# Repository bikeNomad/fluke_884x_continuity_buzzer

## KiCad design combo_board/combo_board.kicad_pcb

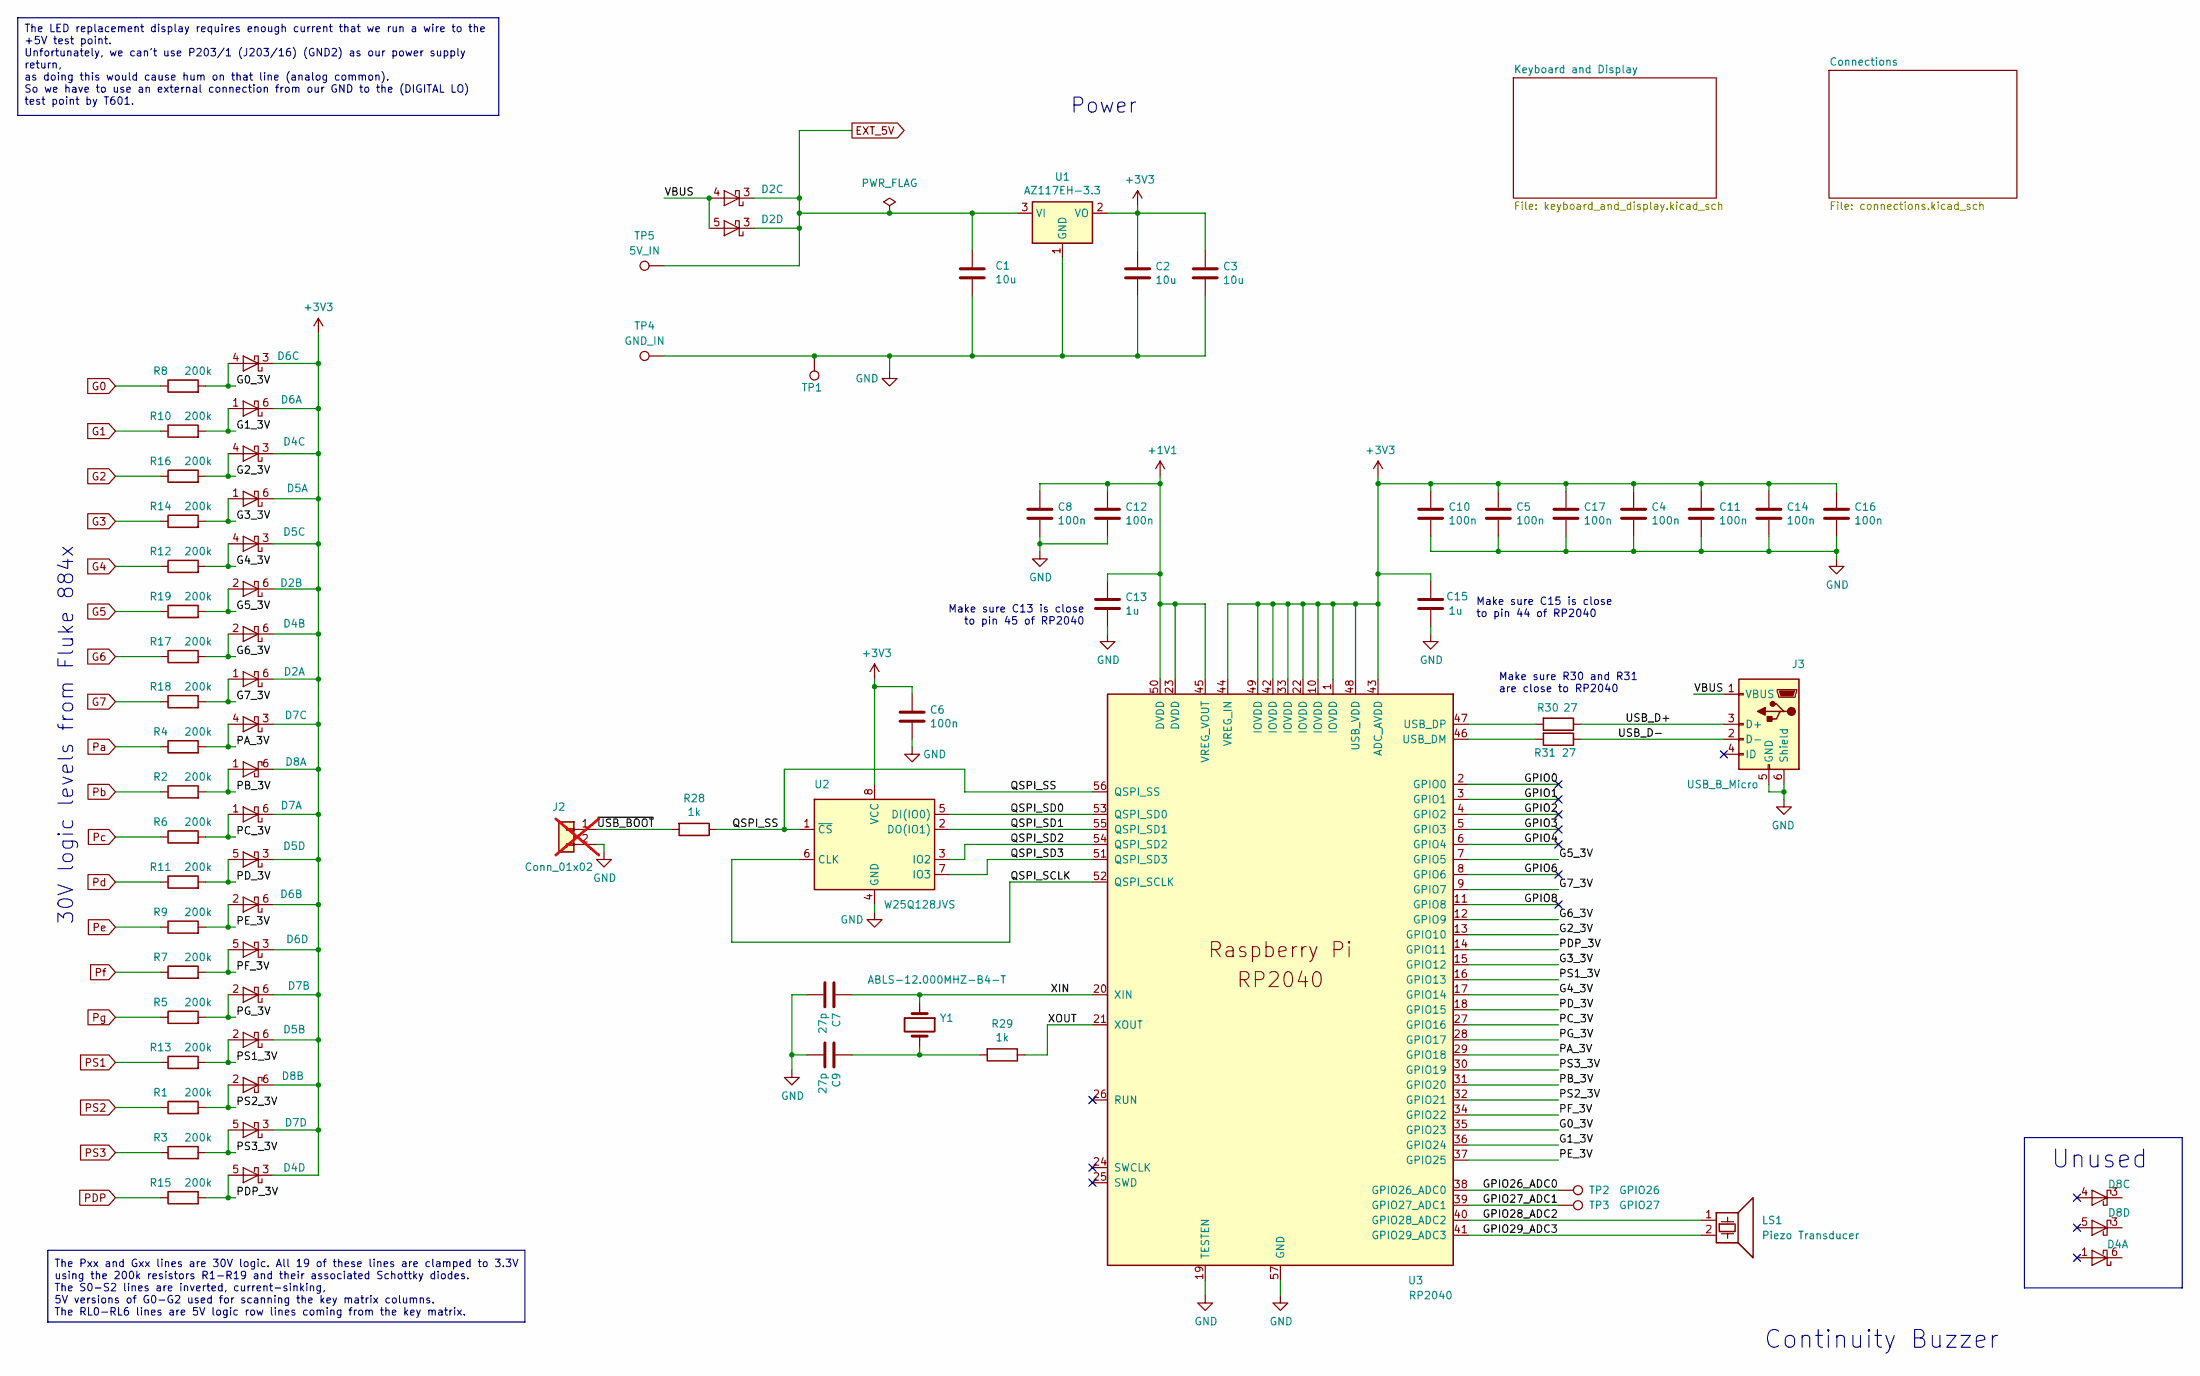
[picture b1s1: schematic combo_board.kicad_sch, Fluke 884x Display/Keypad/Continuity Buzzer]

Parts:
C1, C2, C3: 10u; C_0805_2012Metric; LCSC C15850
C4, C5, C6, C8, C10, C11, C12, C14, C16, C17: 100n; C_0402_1005Metric; LCSC C1525
C7, C9: 27p; C_0402_1005Metric; LCSC C1557
C13, C15: 1u; C_0402_1005Metric; LCSC C52923
D2, D4, D5, D6, D7, D8: BAT54CDW; SOT-363_SC-70-6; LCSC C5240639
J2: Conn_01x02; PinHeader_1x02_P2.54mm_Vertical; LCSC C2685154; not fitted
J3: USB_B_Micro; USB_Micro-B_Molex-105133-0001; LCSC C132563
LS1: Piezo Transducer; Buzzer_17x9RM10; LCSC C360609
R1, R2, R3, R4, R5, R6, R7, R8, R9, R10, R11, R12, R13, R14, R15, R16, R17, R18, R19: 200k; R_0402_1005Metric; LCSC C25764
R28, R29: 1k; R_0402_1005Metric; LCSC C11702
R30, R31: 27; R_0402_1005Metric; LCSC C25156
TP1: TestPoint; TestPoint_Keystone_5019_Minature; LCSC C238131
TP2: GPIO26; TestPoint_THTPad_1.0x1.0mm_Drill0.5mm
TP3: GPIO27; TestPoint_THTPad_1.0x1.0mm_Drill0.5mm
TP4: GND_IN; TestPoint_THTPad_D3.0mm_Drill1.5mm
TP5: 5V_IN; TestPoint_THTPad_D3.0mm_Drill1.5mm
U1: AZ117EH-3.3; SOT-223-3_TabPin2; LCSC C108494
U2: W25Q128JVS; SOIC-8_5.23x5.23mm_P1.27mm; LCSC C97521
U3: RP2040; RP2040-QFN-56; LCSC C2040
Y1: ABLS-12.000MHZ-B4-T; Crystal_SMD_HC49-US; LCSC C326543

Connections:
+1V1: C8.1, C12.1, C13.1, U3.23 (DVDD), U3.45 (VREG_VOUT), U3.50 (DVDD)
+3V3: C2.1, C3.1, C4.1, C5.1, C6.1, C10.1, C11.1, C14.1, C15.1, C16.1, C17.1, D2.6 (K), D4.3 (K), D4.6 (K), D5.3 (K), D5.6 (K), D6.3 (K), D6.6 (K), D7.3 (K), D7.6 (K), D8.6 (K), U1.2 (VO), U2.8 (VCC), U3.1 (IOVDD), U3.10 (IOVDD), U3.22 (IOVDD), U3.33 (IOVDD), U3.42 (IOVDD), U3.43 (ADC_AVDD), U3.44 (VREG_IN), U3.48 (USB_VDD), U3.49 (IOVDD)
/G0_3V: D6.4 (A), R8.2, U3.35 (GPIO23)
/G1_3V: D6.1 (A), R10.2, U3.36 (GPIO24)
/G2_3V: D4.4 (A), R16.2, U3.13 (GPIO10)
/G3_3V: D5.1 (A), R14.2, U3.15 (GPIO12)
/G4_3V: D5.4 (A), R12.2, U3.17 (GPIO14)
/G5_3V: D2.2 (A), R19.2, U3.7 (GPIO5)
/G6_3V: D4.2 (A), R17.2, U3.12 (GPIO9)
/G7_3V: D2.1 (A), R18.2, U3.9 (GPIO7)
/GPIO0: U3.2 (GPIO0)
/GPIO1: U3.3 (GPIO1)
/GPIO2: U3.4 (GPIO2)
/GPIO3: U3.5 (GPIO3)
/GPIO4: U3.6 (GPIO4)
/GPIO6: U3.8 (GPIO6)
/GPIO8: U3.11 (GPIO8)
/GPIO26_ADC0: TP2.1, U3.38 (GPIO26_ADC0)
/GPIO27_ADC1: TP3.1, U3.39 (GPIO27_ADC1)
/GPIO28_ADC2: LS1.1, U3.40 (GPIO28_ADC2)
/GPIO29_ADC3: LS1.2, U3.41 (GPIO29_ADC3)
/PA_3V: D7.4 (A), R4.2, U3.29 (GPIO18)
/PB_3V: D8.1 (A), R2.2, U3.31 (GPIO20)
/PC_3V: D7.1 (A), R6.2, U3.27 (GPIO16)
/PDP_3V: D4.5 (A), R15.2, U3.14 (GPIO11)
/PD_3V: D5.5 (A), R11.2, U3.18 (GPIO15)
/PE_3V: D6.2 (A), R9.2, U3.37 (GPIO25)
/PF_3V: D6.5 (A), R7.2, U3.34 (GPIO22)
/PG_3V: D7.2 (A), R5.2, U3.28 (GPIO17)
/PS1_3V: D5.2 (A), R13.2, U3.16 (GPIO13)
/PS2_3V: D8.2 (A), R1.2, U3.32 (GPIO21)
/PS3_3V: D7.5 (A), R3.2, U3.30 (GPIO19)
/QSPI_SCLK: U2.6 (CLK), U3.52 (QSPI_SCLK)
/QSPI_SD0: U2.5 (DI(IO0)), U3.53 (QSPI_SD0)
/QSPI_SD1: U2.2 (DO(IO1)), U3.55 (QSPI_SD1)
/QSPI_SD2: U2.3 (IO2), U3.54 (QSPI_SD2)
/QSPI_SD3: U2.7 (IO3), U3.51 (QSPI_SD3)
/QSPI_SS: R28.1, U2.1 (~CS), U3.56 (QSPI_SS)
/USB_D+: J3.3 (D+), R30.1
/USB_D-: J3.2 (D-), R31.1
/VBUS: D2.4 (A), D2.5 (A), J3.1 (VBUS)
/XIN: C7.1, U3.20 (XIN), Y1.1
/XOUT: R29.1, U3.21 (XOUT)
/~USB_BOOT: J2.1, R28.2
EXT_5V: C1.1, D2.3 (K), TP5.1, U1.3 (VI); also elsewhere on the board
G0: R8.1; also elsewhere on the board
G1: R10.1; also elsewhere on the board
G2: R16.1; also elsewhere on the board
G3: R14.1; also elsewhere on the board
G4: R12.1; also elsewhere on the board
G5: R19.1; also elsewhere on the board
G6: R17.1; also elsewhere on the board
G7: R18.1; also elsewhere on the board
GND: C1.2, C2.2, C3.2, C4.2, C5.2, C6.2, C7.2, C8.2, C9.2, C10.2, C11.2, C12.2, C13.2, C14.2, C15.2, C16.2, C17.2, J2.2, J3.5 (GND), J3.6 (Shield), TP1.1, TP4.1, U1.1 (GND), U2.4 (GND), U3.19 (TESTEN), U3.57 (GND); also elsewhere on the board
unnamed: C9.1, R29.2, Y1.2
unnamed: R31.2, U3.46 (USB_DM)
unnamed: R30.2, U3.47 (USB_DP)
PDP: R15.1; also elsewhere on the board
PS1: R13.1; also elsewhere on the board
PS2: R1.1; also elsewhere on the board
PS3: R3.1; also elsewhere on the board
Pa: R4.1; also elsewhere on the board
Pb: R2.1; also elsewhere on the board
Pc: R6.1; also elsewhere on the board
Pd: R11.1; also elsewhere on the board
Pe: R9.1; also elsewhere on the board
Pf: R7.1; also elsewhere on the board
Pg: R5.1; also elsewhere on the board

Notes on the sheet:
The LED replacement display requires enough current that we run a wire to the +5V test point. Unfortunately, we can't use P203/1 (J203/16) (GND2) as our power supply return, as doing this would cause hum on that line (analog common). So we have to use an external connection from our GND to the (DIG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
The Pxx and Gxx lines are 30V logic. All 19 of these lines are clamped to 3.3V using the 200k resistors R1-R19 and their associated Schottky diodes. The S0-S2 lines are inverted, current-sinking, 5V versions of G0-G2 used for scanning the key matrix columns. The RL0-RL6 lines are 5V logic row lines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
Unused
Power
30V logic levels from Fluke 884x
Make sure C15 is close to pin 44 of RP2040
Make sure R30 and R31 are close to RP2040
Make sure C13 is close to pin 45 of RP2040
Continuity Buzzer

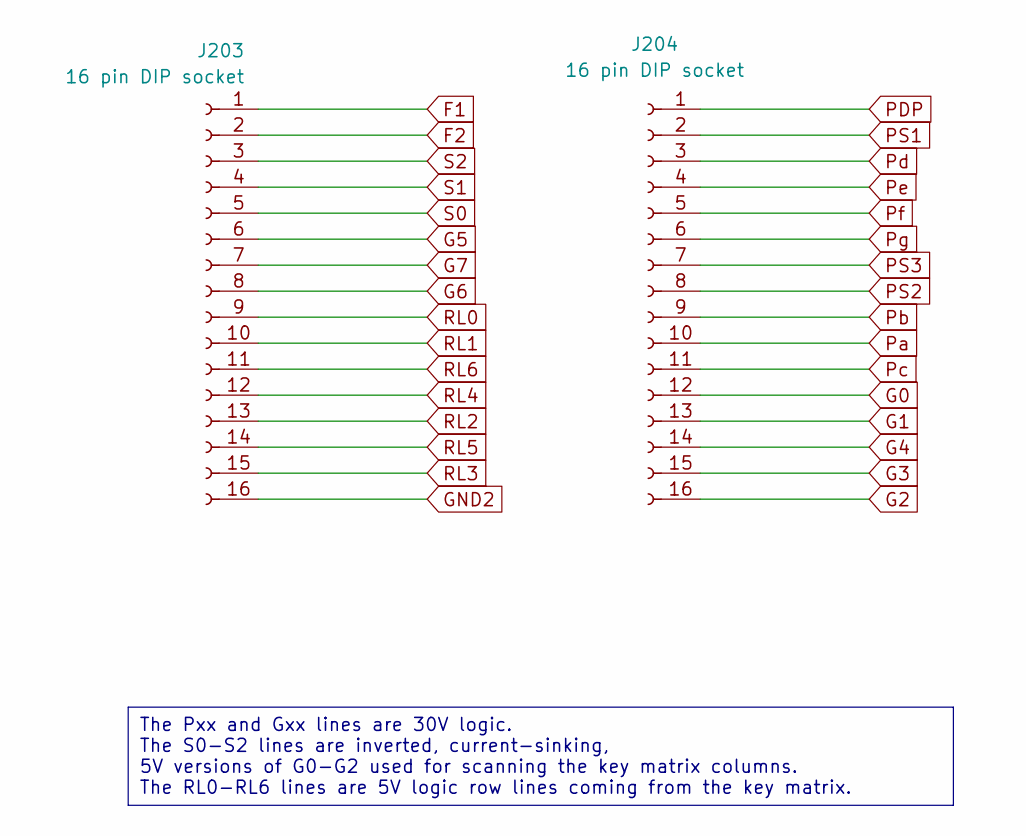
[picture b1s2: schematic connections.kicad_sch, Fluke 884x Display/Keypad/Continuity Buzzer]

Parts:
J203, J204: 16 pin DIP socket; DIP-16_W7.62mm_Socket; LCSC C157594

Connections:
F1: J203.1; also elsewhere on the board
F2: J203.2; also elsewhere on the board
G0: J204.12; also elsewhere on the board
G1: J204.13; also elsewhere on the board
G2: J204.16; also elsewhere on the board
G3: J204.15; also elsewhere on the board
G4: J204.14; also elsewhere on the board
G5: J203.6; also elsewhere on the board
G6: J203.8; also elsewhere on the board
G7: J203.7; also elsewhere on the board
GND2: J203.16
PDP: J204.1; also elsewhere on the board
PS1: J204.2; also elsewhere on the board
PS2: J204.8; also elsewhere on the board
PS3: J204.7; also elsewhere on the board
Pa: J204.10; also elsewhere on the board
Pb: J204.9; also elsewhere on the board
Pc: J204.11; also elsewhere on the board
Pd: J204.3; also elsewhere on the board
Pe: J204.4; also elsewhere on the board
Pf: J204.5; also elsewhere on the board
Pg: J204.6; also elsewhere on the board
RL0: J203.9; also elsewhere on the board
RL1: J203.10; also elsewhere on the board
RL2: J203.13; also elsewhere on the board
RL3: J203.15; also elsewhere on the board
RL4: J203.12; also elsewhere on the board
RL5: J203.14; also elsewhere on the board
RL6: J203.11; also elsewhere on the board
S0: J203.5; also elsewhere on the board
S1: J203.4; also elsewhere on the board
S2: J203.3; also elsewhere on the board

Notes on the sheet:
The Pxx and Gxx lines are 30V logic. The S0-S2 lines are inverted, current-sinking, 5V versions of G0-G2 used for scanning the key matrix columns. The RL0-RL6 lines are 5V logic row lines coming from the key matrix.

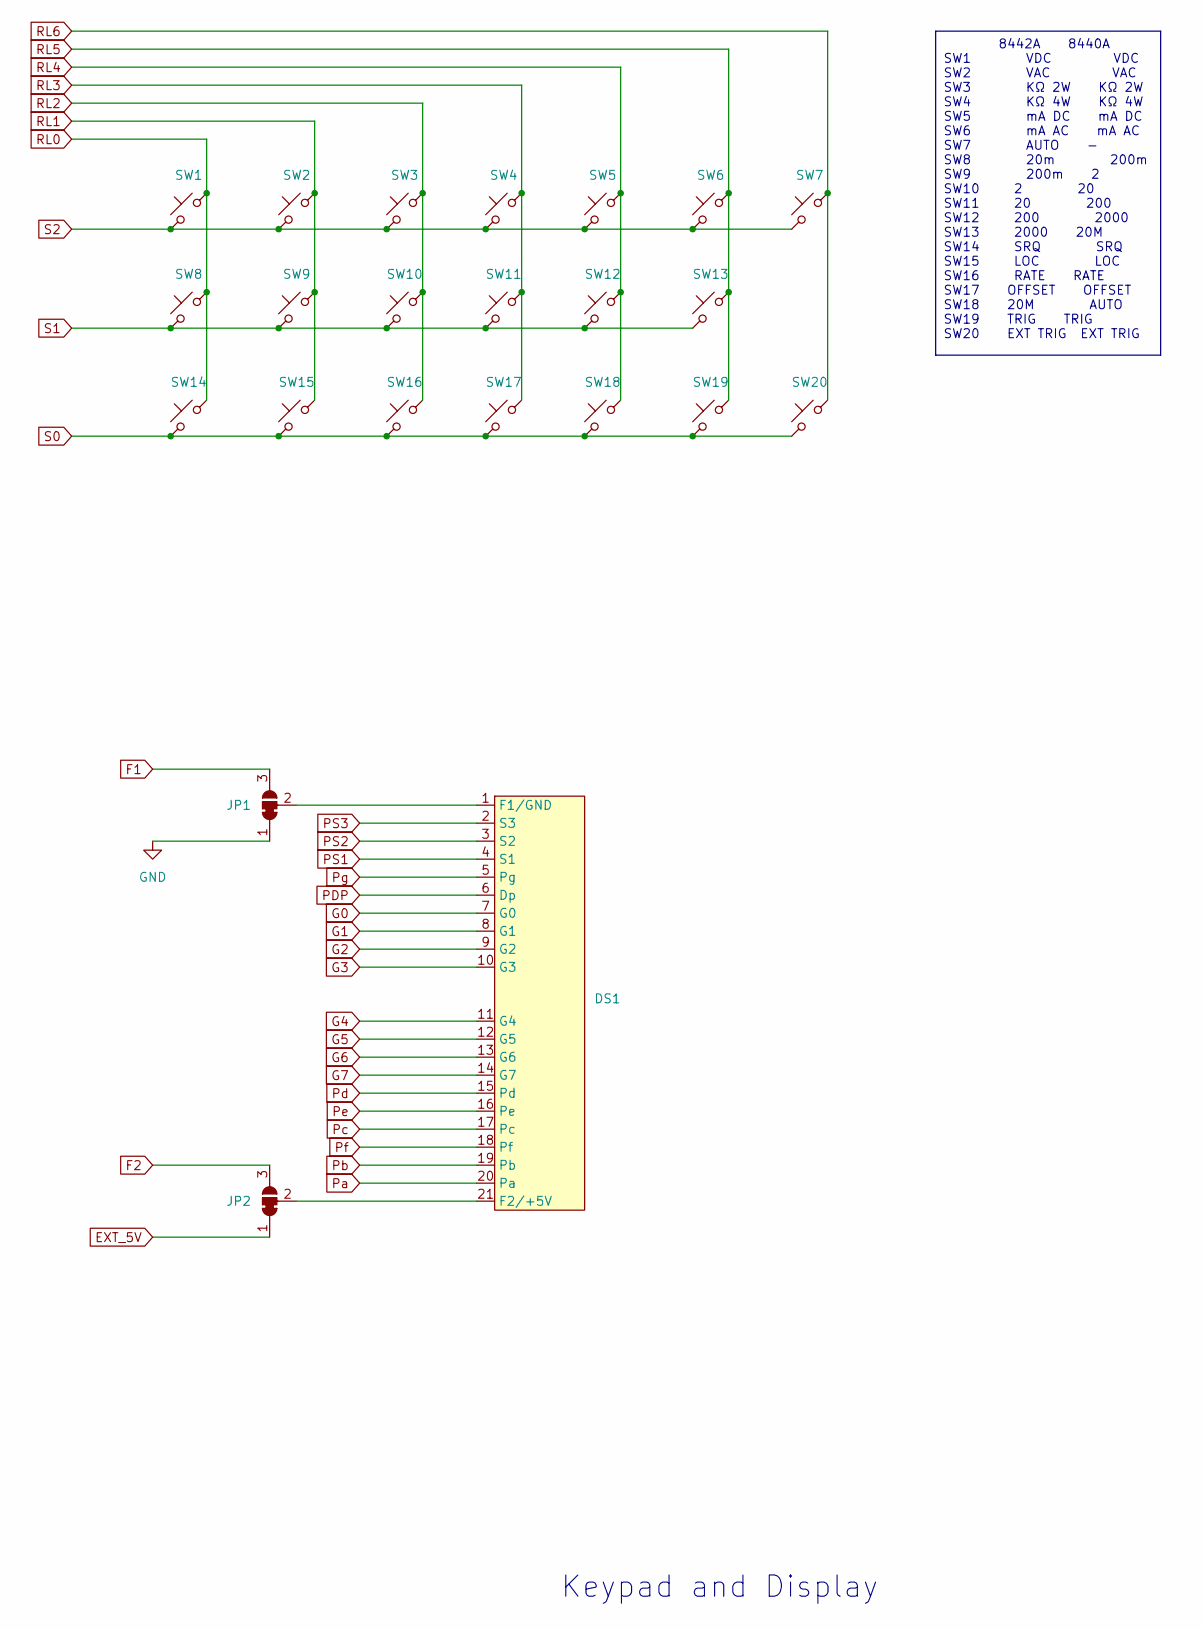
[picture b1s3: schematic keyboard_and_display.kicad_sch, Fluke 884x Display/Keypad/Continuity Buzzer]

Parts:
DS1: fluke_884x_display
JP1, JP2: SolderJumper_3_Bridged12; SolderJumper-3_P1.3mm_Bridged12_Pad1.0x1.5mm_NumberLabels
SW1, SW2, SW3, SW4, SW5, SW6, SW7, SW8, SW9, SW10, SW11, SW12, SW13, SW14, SW15, SW16, SW17, SW18, SW19, SW20: SW_Push_45deg; fluke_keypad_contact

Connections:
EXT_5V: JP2.1 (A); also elsewhere on the board
F1: JP1.3 (B); also elsewhere on the board
F2: JP2.3 (B); also elsewhere on the board
G0: DS1.7 (G0); also elsewhere on the board
G1: DS1.8 (G1); also elsewhere on the board
G2: DS1.9 (G2); also elsewhere on the board
G3: DS1.10 (G3); also elsewhere on the board
G4: DS1.11 (G4); also elsewhere on the board
G5: DS1.12 (G5); also elsewhere on the board
G6: DS1.13 (G6); also elsewhere on the board
G7: DS1.14 (G7); also elsewhere on the board
GND: JP1.1 (A); also elsewhere on the board
unnamed: DS1.1 (F1/GND), JP1.2 (C)
unnamed: DS1.21 (F2/+5V), JP2.2 (C)
PDP: DS1.6 (Dp); also elsewhere on the board
PS1: DS1.4 (S1); also elsewhere on the board
PS2: DS1.3 (S2); also elsewhere on the board
PS3: DS1.2 (S3); also elsewhere on the board
Pa: DS1.20 (Pa); also elsewhere on the board
Pb: DS1.19 (Pb); also elsewhere on the board
Pc: DS1.17 (Pc); also elsewhere on the board
Pd: DS1.15 (Pd); also elsewhere on the board
Pe: DS1.16 (Pe); also elsewhere on the board
Pf: DS1.18 (Pf); also elsewhere on the board
Pg: DS1.5 (Pg); also elsewhere on the board
RL0: SW1.1, SW8.1, SW14.1; also elsewhere on the board
RL1: SW2.1, SW9.1, SW15.1; also elsewhere on the board
RL2: SW3.1, SW10.1, SW16.1; also elsewhere on the board
RL3: SW4.1, SW11.1, SW17.1; also elsewhere on the board
RL4: SW5.1, SW12.1, SW18.1; also elsewhere on the board
RL5: SW6.1, SW13.1, SW19.1; also elsewhere on the board
RL6: SW7.1, SW20.1; also elsewhere on the board
S0: SW14.2, SW15.2, SW16.2, SW17.2, SW18.2, SW19.2, SW20.2; also elsewhere on the board
S1: SW8.2, SW9.2, SW10.2, SW11.2, SW12.2, SW13.2; also elsewhere on the board
S2: SW1.2, SW2.2, SW3.2, SW4.2, SW5.2, SW6.2, SW7.2; also elsewhere on the board

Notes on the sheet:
8442A 8440A SW1 VDC VDC SW2 VAC VAC SW3 KΩ 2W KΩ 2W SW4 KΩ 4W KΩ 4W SW5 mA DC mA DC SW6 mA AC mA AC SW7 AUTO - SW8 20m 200m SW9 200m 2 SW10 2 20 SW11 20 200 SW12 200 2000 SW13 2000 20M SW14 SRQ SRQ SW15 LOC LOC SW16 RATE RATE SW17 OFFSET OFFSET SW18 20M AUTO SW19 TRIG TRIG SW20 EXT TRIG EXT TRIG
Keypad and Display

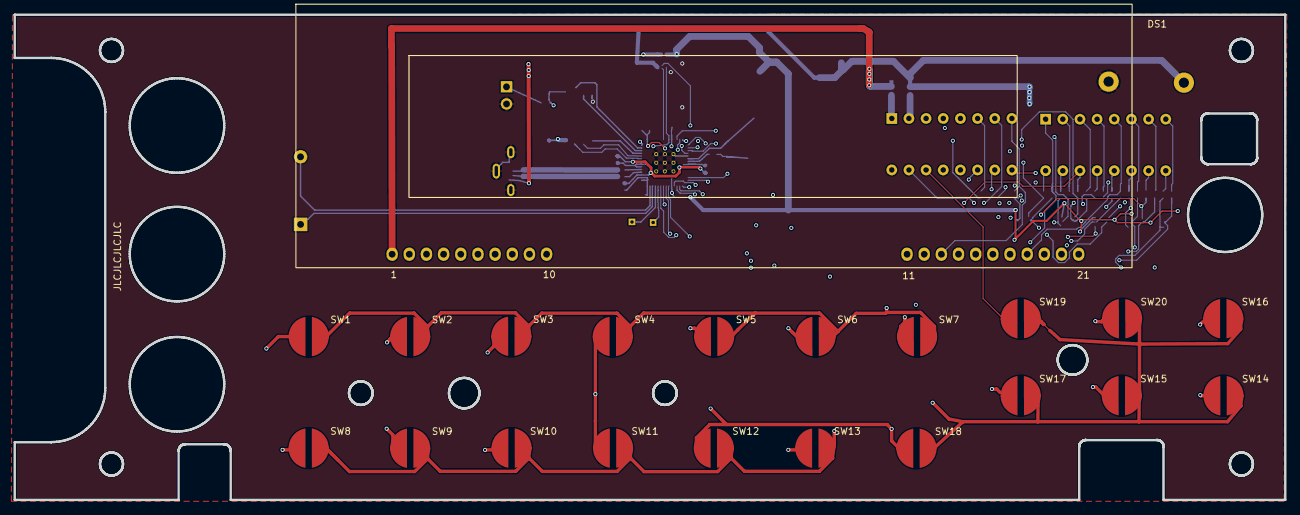
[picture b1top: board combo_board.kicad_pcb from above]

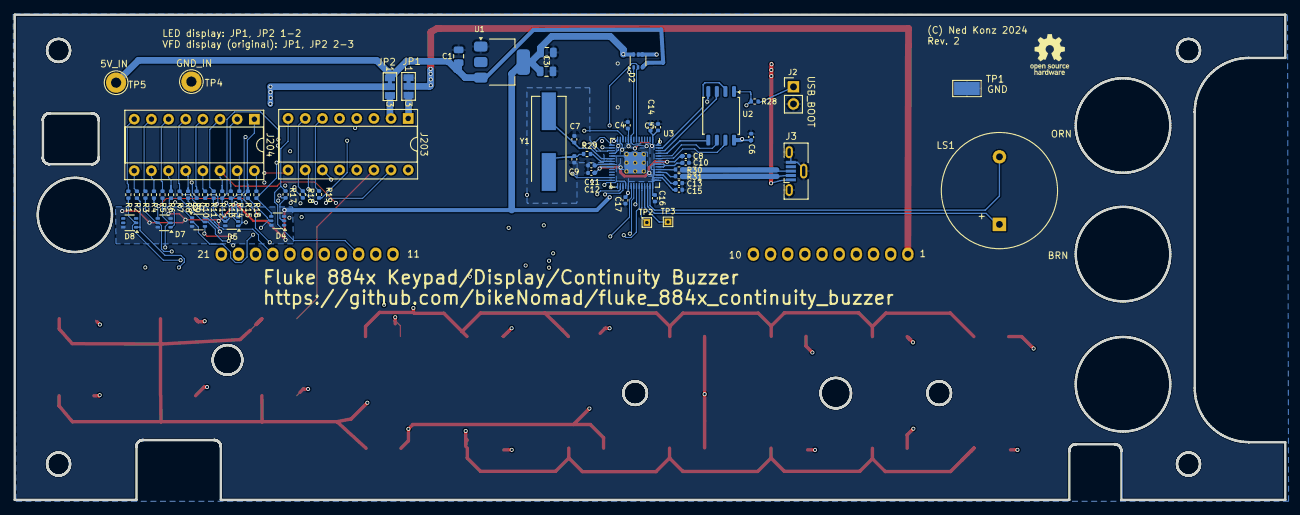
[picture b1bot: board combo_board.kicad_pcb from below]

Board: 4 copper layers, 188.0 x 71.8 mm, 83 parts (62 on the bottom side), 75 nets.

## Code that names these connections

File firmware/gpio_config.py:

# Definitions of GPIO pin names and numbers
from micropython import const
from machine import Pin, mem32

# GPIO pin names for the RP2040 microcontroller pins connected to the Fluke multimeter signals.
# The pin numbers are the GPIO pin numbers on the RP2040.
# The pin names are the names used in the Fluke 8840A/8842A multimeter documentation.
# RL0-RL6 are the switch return lines for the matrix keyboard and are active-low signals.
# G0-G7 are the digit select lines for the 7-segment display and are active-high signals.
# PA-PG are the segment select lines for the 7-segment display and are active-high signals.
# PDP is the decimal point signal for the 7-segment display and is an active-high signal.
# PS1-PS3 are the segment select lines for the extra words on the display and are active-high signals.
PIN_G5 = const(5)
PIN_G7 = const(7)
PIN_G6 = const(9)
PIN_G2 = const(10)
PIN_PDP = const(11)
PIN_G3 = const(12)
PIN_PS1 = const(13)
PIN_G4 = const(14)
PIN_PD = const(15)
PIN_PC = const(16)
PIN_PG = const(17)
PIN_PA = const(18)
PIN_PS3 = const(19)
PIN_PB = const(20)
PIN_PS2 = const(21)
PIN_PF = const(22)
PIN_G0 = const(23)
PIN_G1 = const(24)
PIN_PE = const(25)

# Two GPIO pins are used to drive the piezo buzzer.
PIN_BUZZER1 = const(28)
PIN_BUZZER2 = const(29)

INPUT_PIN_MASK = const(0x03FFFFFF)  # mask for the 26 GPIO pins used as inputs

# Address of the GPIO input register on the RP2040
GPIO_IN_ADDR = const(0xD0000004)
GPIO_OUT_ADDR = const(0xD0000010)
GPIO_OE_ADDR = const(0xD0000020)
GPIO_OE_SET_ADDR = const(0xD0000024)
GPIO_OE_CLEAR_ADDR = const(0xD0000028)

# Pins 0-4,6,8 are unused
UNUSED_PINS = (0, 1, 2, 3, 4, 6, 8)
# Two spare pins 26 and 27
SPARE_PINS = (26, 27)

PULL_NONE = 0 # not in Pin
# pull-up and pull-down resistors are 50-80KΩ.
# board has 200Ω series resistors on 30V inputs
# with diode clamps to 3.3V.

def initialize_pins():
    # Set all the GPIO pins to inputs with pull-down resistors.
    for pin in range(26):
        Pin(pin, Pin.IN, Pin.PULL_DOWN)

    for pin in SPARE_PINS:
        Pin(pin, Pin.OUT, value=0)

    # Set the piezo buzzer pins to outputs.
    Pin(PIN_BUZZER1, Pin.OUT).value(0)
    Pin(PIN_BUZZER2, Pin.OUT).value(0)


# Read all 30 of the GPIO pin states at once.
def read_gpio_pins() -> int:
    return mem32[GPIO_IN_ADDR]


# Write a selected subset of the GPIO pins.
# The mask selects which bits to write.
def write_gpio_pins(mask, value) -> None:
    # set the GPIO output direction to output
    mem32[GPIO_OE_SET_ADDR] = mask
    mem32[GPIO_OUT_ADDR] = value


# Stop writing the masked outputs.
def dont_write_gpio_pins(mask):
    mem32[GPIO_OE_CLEAR_ADDR] = mask


# Create a bit mask for a given bit number
def BIT(n):
    return 1 << n

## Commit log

2024-01-29 Added LCSC refs
2024-01-29 Added PDF of front of board and JLCPCB files
2024-01-30 Updated text; fixed silk
2024-01-30 Added JLCPCB image of parts placement
2024-01-31 Moved Kicad files into hardware directory
2024-01-31 Added initial code
2024-02-09 Fixed decode.py
2024-02-10 WIP: made board shorter
2024-02-10 Getting FW to work
2024-02-11 WIP: shortened board, added driver for keypad signals.
    Also changed 30V R values.
2024-02-11 Added QR code; fixed JLC refs
2024-02-11 Update JLC part numbers
2024-02-11 Add board image
2024-02-11 Change R1-R19 to 200k
2024-02-11 WIP: work on keypad.
2024-02-11 Sent JLC order in
2024-02-24 added release_keypad()
2024-02-25 Got fw working
2024-02-25 Distinguish rate M from Meg
2024-02-25 Add PDF of schematic.
    Also correct text in schematic.
2024-02-25 Add display board photo
2024-06-19 Removed bus buffer
2024-08-24 updating for rev3
2024-08-24 Add model for DIP-16 with pins both sides
2024-08-24 Add schematic PDF
2024-08-25 Add final parts; generate JLCPCB data
2024-09-14 Made JLCPCB order
2024-09-14 Removed keypad support
2024-09-14 Added 3D model of spacer and SVG of adhesive rings
2024-09-15 Remove keypad GPIO
2024-09-16 Updated PCB layout to shorten board
2024-09-16 Exclude plugs and USB BOOT header from production
2024-09-19 Change to using external GND connection
2024-09-27 Ordered from JLCPCB; add combo board project
2024-09-27 Add mechanical files
2024-09-27 WIP: added keypad switches
2024-09-27 Ready to route
2024-09-30 Moved GND, +5V inputs to L Rear of board
2024-10-02 Got JLCPCB order ready
2024-10-18 Move GND terminal to clear chassis
2024-10-18 Enable pull-down resistors on 30V input pins.
    Also make DEBUG configurable easily.
